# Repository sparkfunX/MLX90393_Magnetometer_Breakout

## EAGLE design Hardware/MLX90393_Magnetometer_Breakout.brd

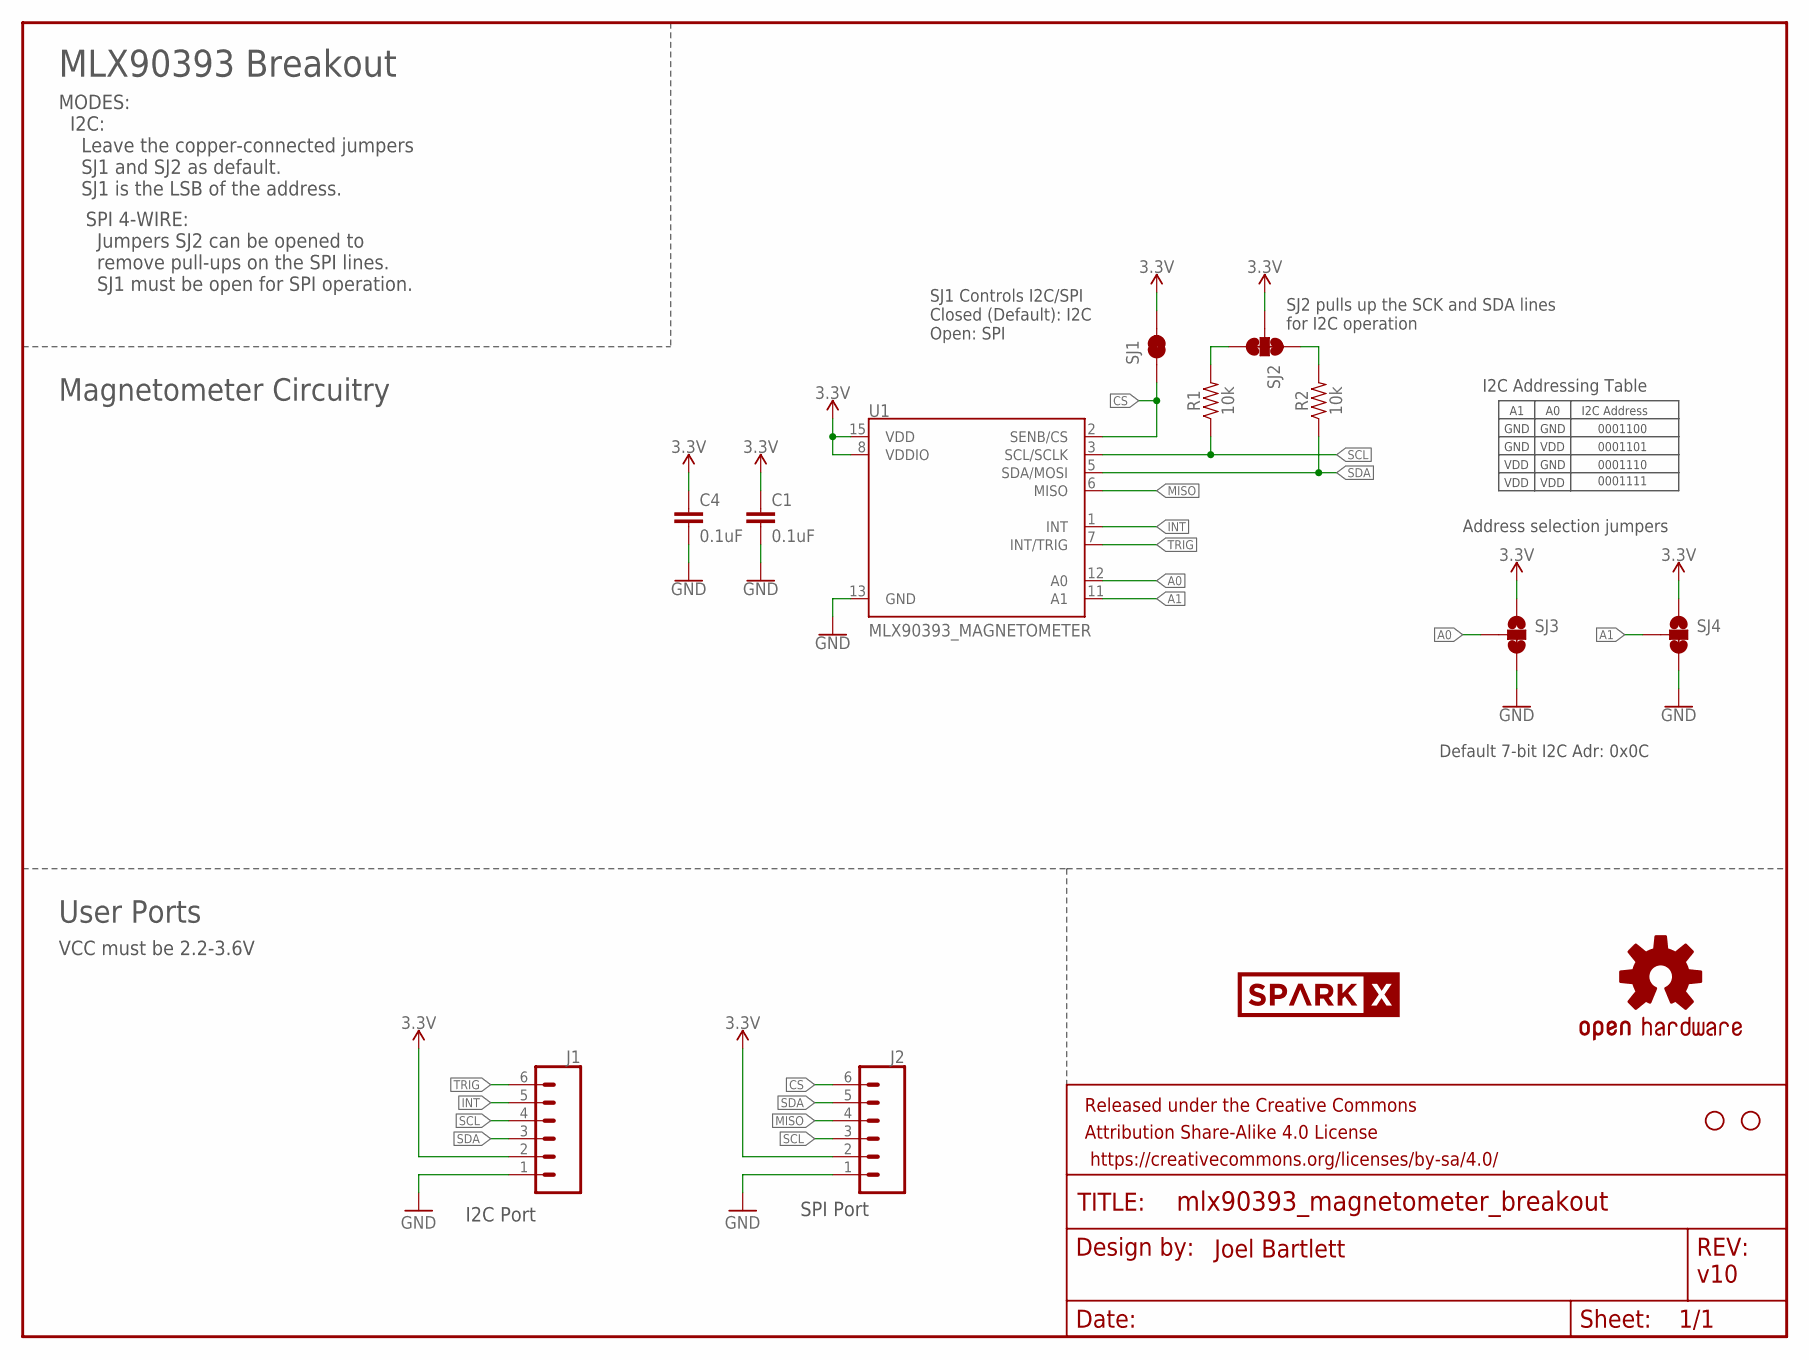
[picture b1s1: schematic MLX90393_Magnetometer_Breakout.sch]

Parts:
C1, C4: 0.1uF; 0603
FRAME2: FRAME-LETTER; CREATIVE_COMMONS
J1, J2: CONN_06NO_SILK_FEMALE_PTH; 1X06_NO_SILK
JP3, JP4: STAND-OFF
R1, R2: 10k; 0603
SJ1: JUMPER-SMT_2_NC_TRACE_SILK; SMT-JUMPER_2_NC_TRACE_SILK
SJ2: JUMPER-PAD-3-NC_BY_TRACE; PAD-JUMPER-3-3OF3_NC_BY_TRACE_YES_SILK_FULL_BOX
SJ3, SJ4: JUMPER-SMT_3_1-NC_TRACE_SILK; SMT-JUMPER_3_1-NC_TRACE_SILK
U1: MLX90393_MAGNETOMETER; QFN-16
U$1: OSHW-LOGOS; OSHW-LOGO-S
U$2: SPARKX-LOGO2; SPARKX-TINY

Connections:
3.3V: C1.1, C4.1, J1.2, J2.2, SJ1.2, SJ2.2, SJ3.1, SJ4.1, U1.8 (VDDIO), U1.15 (VDD)
A0: SJ3.2, U1.12 (A0)
A1: SJ4.2, U1.11 (A1)
CS: J2.6, SJ1.1, U1.2 (SENB/CS)
GND: C1.2, C4.2, J1.1, J2.1, SJ3.3, SJ4.3, U1.13 (GND)
INT: J1.5, U1.1 (INT)
MISO: J2.4, U1.6 (MISO)
unnamed: R2.2, SJ2.1
unnamed: R1.2, SJ2.3
SCL: J1.4, J2.3, R1.1, U1.3 (SCL/SCLK)
SDA: J1.3, J2.5, R2.1, U1.5 (SDA/MOSI)
TRIG: J1.6, U1.7 (INT/TRIG)

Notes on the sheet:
Address selection jumpers
v10
Joel Bartlett
MLX90393 Breakout
SJ2 pulls up the SCK and SDA lines for I2C operation
MODES: I2C: Leave the copper-connected jumpers SJ1 and SJ2 as default. SJ1 is the LSB of the address.
Magnetometer Circuitry
User Ports
VCC must be 2.2-3.6V
SJ1 Controls I2C/SPI Closed (Default): I2C Open: SPI
I2C Port
SPI Port
I2C Address
0001100
0001101
0001110
0001111
GND
VDD
SPI 4-WIRE: Jumpers SJ2 can be opened to remove pull-ups on the SPI lines. SJ1 must be open for SPI operation.
I2C Addressing Table
Default 7-bit I2C Adr: 0x0C

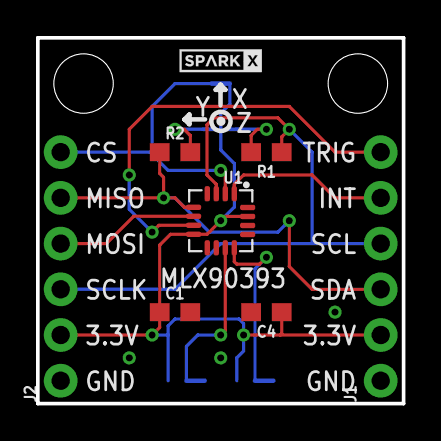
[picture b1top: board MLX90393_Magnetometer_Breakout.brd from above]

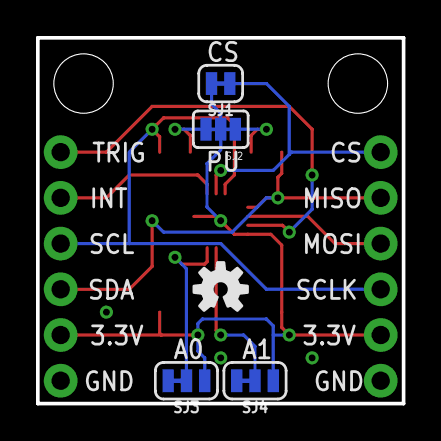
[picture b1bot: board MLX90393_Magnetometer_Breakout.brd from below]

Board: 2 copper layers, 20.3 x 20.3 mm, 16 parts (5 on the bottom side), 12 nets.

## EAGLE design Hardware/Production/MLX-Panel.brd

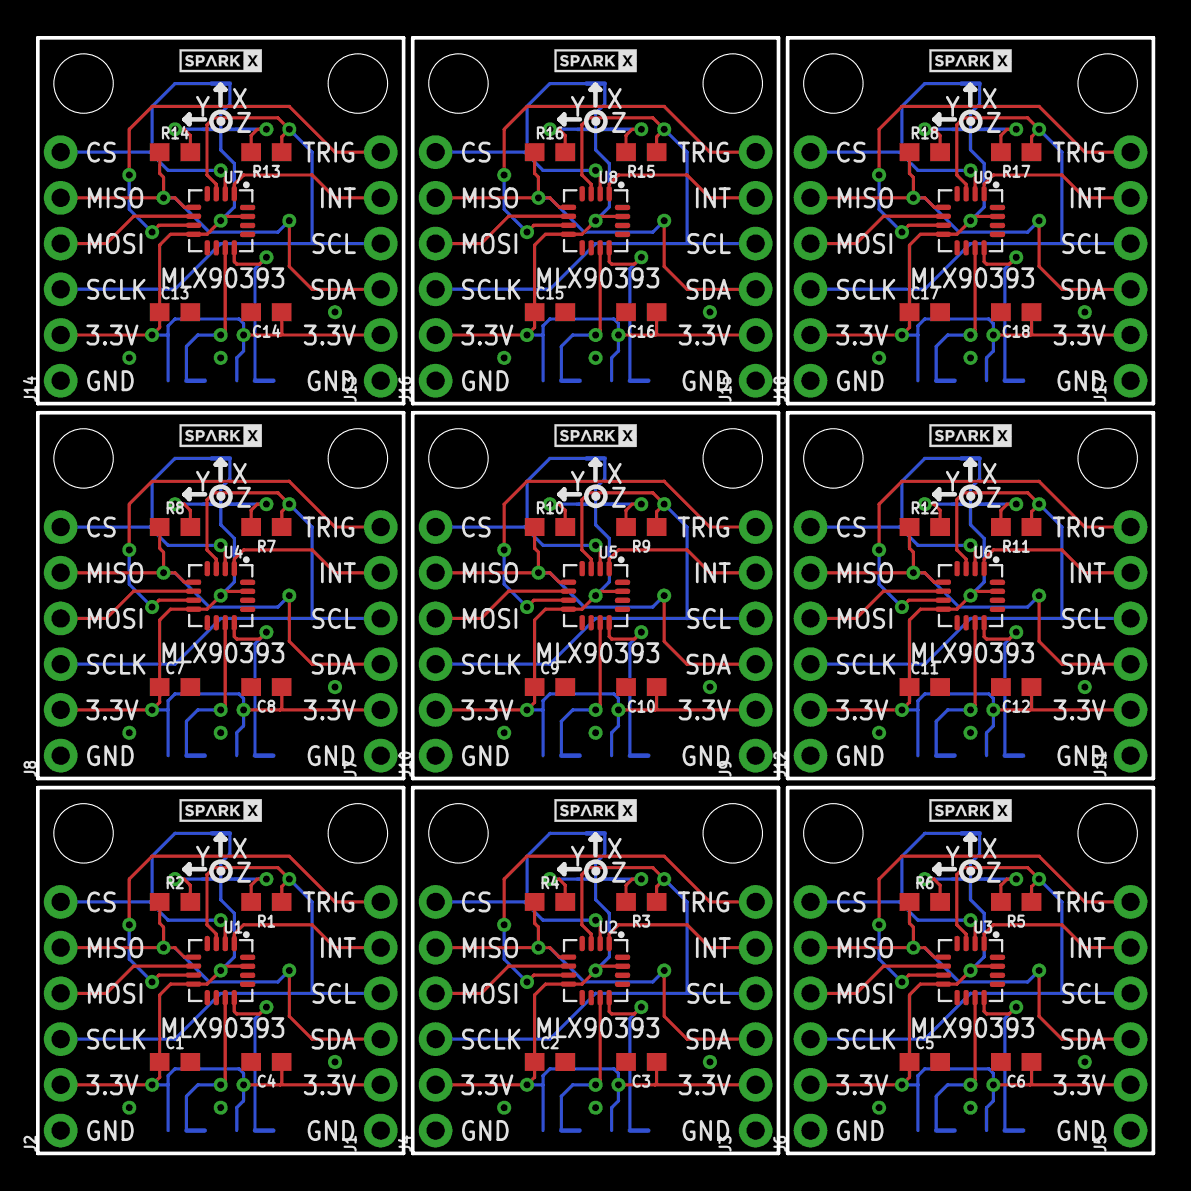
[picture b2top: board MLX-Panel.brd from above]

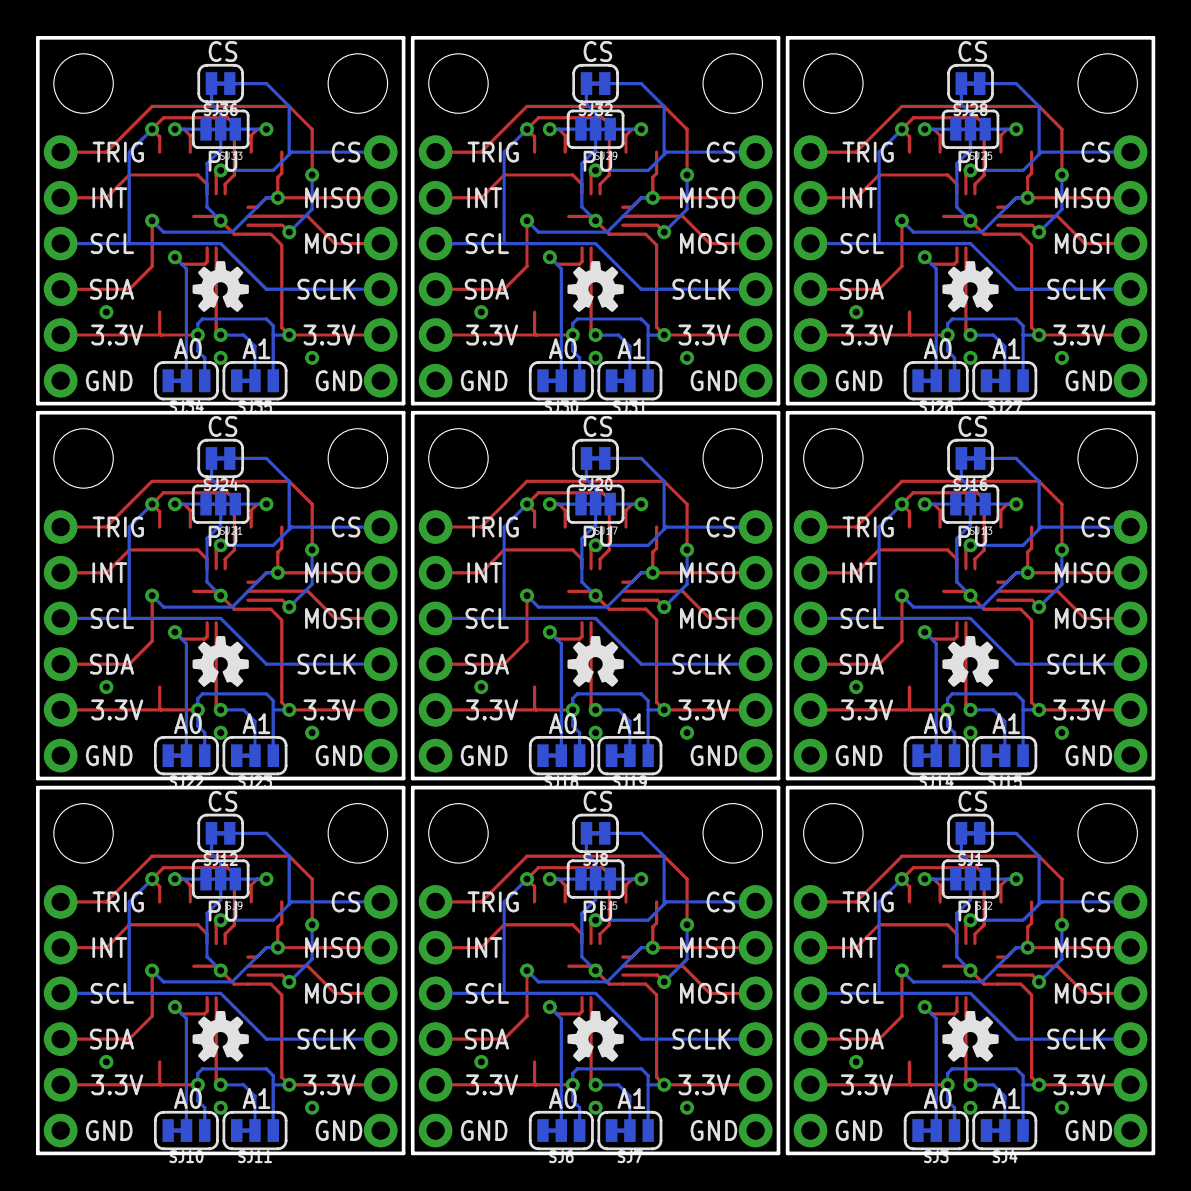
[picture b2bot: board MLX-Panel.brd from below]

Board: 2 copper layers, 62.0 x 62.0 mm, 135 parts (45 on the bottom side), 108 nets.

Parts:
C1, C2, C3, C4, C5, C6, C7, C8, C9, C10, C11, C12, C13, C14, C15, C16, C17, C18: 0.1uF; 0603
J1, J2, J3, J4, J5, J6, J7, J8, J9, J10, J11, J12, J13, J14, J15, J16, J17, J18: 1X06_NO_SILK
JP1, JP2, JP3, JP4, JP5, JP6, JP7, JP8, JP9, JP10, JP11, JP12, JP13, JP14, JP15, JP16, JP17, JP18: STAND-OFF
R1, R2, R3, R4, R5, R6, R7, R8, R9, R10, R11, R12, R13, R14, R15, R16, R17, R18: 10k; 0603
SJ1, SJ8, SJ12, SJ16, SJ20, SJ24, SJ28, SJ32, SJ36: SMT-JUMPER_2_NC_TRACE_SILK
SJ2, SJ5, SJ9, SJ13, SJ17, SJ21, SJ25, SJ29, SJ33: PAD-JUMPER-3-3OF3_NC_BY_TRACE_YES_SILK_FULL_BOX
SJ3, SJ4, SJ6, SJ7, SJ10, SJ11, SJ14, SJ15, SJ18, SJ19, SJ22, SJ23, SJ26, SJ27, SJ30, SJ31, SJ34, SJ35: SMT-JUMPER_3_1-NC_TRACE_SILK
U1, U2, U3, U4, U5, U6, U7, U8, U9: MLX90393_MAGNETOMETER; QFN-16
U$1, U$3, U$5, U$7, U$9, U$11, U$13, U$15, U$17: OSHW-LOGOS; OSHW-LOGO-S
U$2, U$4, U$6, U$8, U$10, U$12, U$14, U$16, U$18: SPARKX-LOGO2; SPARKX-TINY

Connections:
3.3V: C1.1, C4.1, J1.2, J2.2, SJ1.2, SJ2.2, SJ3.1, SJ4.1, U1.8, U1.15
3.3V1: C2.1, C3.1, J3.2, J4.2, SJ5.2, SJ6.1, SJ7.1, SJ8.2, U2.8, U2.15
3.3V2: C5.1, C6.1, J5.2, J6.2, SJ9.2, SJ10.1, SJ11.1, SJ12.2, U3.8, U3.15
3.3V3: C7.1, C8.1, J7.2, J8.2, SJ13.2, SJ14.1, SJ15.1, SJ16.2, U4.8, U4.15
3.3V4: C9.1, C10.1, J9.2, J10.2, SJ17.2, SJ18.1, SJ19.1, SJ20.2, U5.8, U5.15
3.3V5: C11.1, C12.1, J11.2, J12.2, SJ21.2, SJ22.1, SJ23.1, SJ24.2, U6.8, U6.15
3.3V6: C13.1, C14.1, J13.2, J14.2, SJ25.2, SJ26.1, SJ27.1, SJ28.2, U7.8, U7.15
3.3V7: C15.1, C16.1, J15.2, J16.2, SJ29.2, SJ30.1, SJ31.1, SJ32.2, U8.8, U8.15
3.3V8: C17.1, C18.1, J17.2, J18.2, SJ33.2, SJ34.1, SJ35.1, SJ36.2, U9.8, U9.15
A0: SJ3.2, U1.12
A1: SJ4.2, U1.11
A2: SJ6.2, U2.12
A3: SJ7.2, U2.11
A4: SJ10.2, U3.12
A5: SJ11.2, U3.11
A6: SJ14.2, U4.12
A7: SJ15.2, U4.11
A8: SJ18.2, U5.12
A9: SJ19.2, U5.11
A10: SJ22.2, U6.12
A11: SJ23.2, U6.11
A12: SJ26.2, U7.12
A13: SJ27.2, U7.11
A14: SJ30.2, U8.12
A15: SJ31.2, U8.11
A16: SJ34.2, U9.12
A17: SJ35.2, U9.11
CS: J2.6, SJ1.1, U1.2
CS1: J4.6, SJ8.1, U2.2
CS2: J6.6, SJ12.1, U3.2
CS3: J8.6, SJ16.1, U4.2
CS4: J10.6, SJ20.1, U5.2
CS5: J12.6, SJ24.1, U6.2
CS6: J14.6, SJ28.1, U7.2
CS7: J16.6, SJ32.1, U8.2
CS8: J18.6, SJ36.1, U9.2
GND: C1.2, C4.2, J1.1, J2.1, SJ3.3, SJ4.3, U1.13
GND1: C2.2, C3.2, J3.1, J4.1, SJ6.3, SJ7.3, U2.13
GND2: C5.2, C6.2, J5.1, J6.1, SJ10.3, SJ11.3, U3.13
GND3: C7.2, C8.2, J7.1, J8.1, SJ14.3, SJ15.3, U4.13
GND4: C9.2, C10.2, J9.1, J10.1, SJ18.3, SJ19.3, U5.13
GND5: C11.2, C12.2, J11.1, J12.1, SJ22.3, SJ23.3, U6.13
GND6: C13.2, C14.2, J13.1, J14.1, SJ26.3, SJ27.3, U7.13
GND7: C15.2, C16.2, J15.1, J16.1, SJ30.3, SJ31.3, U8.13
GND8: C17.2, C18.2, J17.1, J18.1, SJ34.3, SJ35.3, U9.13
INT: J1.5, U1.1
INT1: J3.5, U2.1
INT2: J5.5, U3.1
INT3: J7.5, U4.1
INT4: J9.5, U5.1
INT5: J11.5, U6.1
INT6: J13.5, U7.1
INT7: J15.5, U8.1
INT8: J17.5, U9.1
MISO: J2.4, U1.6
MISO1: J4.4, U2.6
MISO2: J6.4, U3.6
MISO3: J8.4, U4.6
MISO4: J10.4, U5.6
MISO5: J12.4, U6.6
MISO6: J14.4, U7.6
MISO7: J16.4, U8.6
MISO8: J18.4, U9.6
unnamed: R4.2, SJ5.1
unnamed: R3.2, SJ5.3
unnamed: R6.2, SJ9.1
unnamed: R2.2, SJ2.1
unnamed: R1.2, SJ2.3
unnamed: R5.2, SJ9.3
unnamed: R8.2, SJ13.1
unnamed: R7.2, SJ13.3
unnamed: R10.2, SJ17.1
unnamed: R9.2, SJ17.3
unnamed: R12.2, SJ21.1
unnamed: R11.2, SJ21.3
unnamed: R14.2, SJ25.1
unnamed: R13.2, SJ25.3
unnamed: R16.2, SJ29.1
unnamed: R15.2, SJ29.3
unnamed: R18.2, SJ33.1
unnamed: R17.2, SJ33.3
SCL: J1.4, J2.3, R1.1, U1.3
SCL1: J3.4, J4.3, R3.1, U2.3
SCL2: J5.4, J6.3, R5.1, U3.3
SCL3: J7.4, J8.3, R7.1, U4.3
SCL4: J9.4, J10.3, R9.1, U5.3
SCL5: J11.4, J12.3, R11.1, U6.3
SCL6: J13.4, J14.3, R13.1, U7.3
SCL7: J15.4, J16.3, R15.1, U8.3
SCL8: J17.4, J18.3, R17.1, U9.3
SDA: J1.3, J2.5, R2.1, U1.5
SDA1: J3.3, J4.5, R4.1, U2.5
SDA2: J5.3, J6.5, R6.1, U3.5
SDA3: J7.3, J8.5, R8.1, U4.5
SDA4: J9.3, J10.5, R10.1, U5.5
SDA5: J11.3, J12.5, R12.1, U6.5
SDA6: J13.3, J14.5, R14.1, U7.5
SDA7: J15.3, J16.5, R16.1, U8.5
SDA8: J17.3, J18.5, R18.1, U9.5
TRIG: J1.6, U1.7
TRIG1: J3.6, U2.7
TRIG2: J5.6, U3.7
TRIG3: J7.6, U4.7
TRIG4: J9.6, U5.7
TRIG5: J11.6, U6.7
TRIG6: J13.6, U7.7
TRIG7: J15.6, U8.7
TRIG8: J17.6, U9.7

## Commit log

2017-02-02 Ready for Review
2017-02-03 Production layout and panel for review
2017-02-03 Adding bottom silk
2017-02-05 Adding new panel with updated silk and cream
2017-02-06 fixed silk and jumper
2017-02-06 Prelim example code
2017-02-06 Expanding example code
2017-02-07 Fixed QFN-16
2017-02-07 Folder rename
2017-02-07 Bringing back production layout: missing top mask on QFN.
2017-02-07 Removing extra files.
2017-02-07 fixed panel with tstop, pushed berbers
2017-02-07 Tidying example code

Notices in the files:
parts and their libraries:
SparkFun-Aesthetics: Licensing: Creative Commons ShareAlike 4.0 International - https://creativecommons.org/licenses/by-sa/4.0
SparkFun-Aesthetics: Released under the Creative Commons Attribution Share-Alike 4.0 License
SparkFun-Aesthetics: https://creativecommons.org/licenses/by-sa/4.0
